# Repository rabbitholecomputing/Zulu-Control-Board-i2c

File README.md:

# Zulu control board hardware
## zulu-ctrl-board-v1.0-kicad
OLED with rotatory with a push button and two more buttons
with an I2C and an added interrupt line.

This design is derived from "ctrl_board_v1p6" in this project:
https://github.com/PiSCSI/piscsi-hw

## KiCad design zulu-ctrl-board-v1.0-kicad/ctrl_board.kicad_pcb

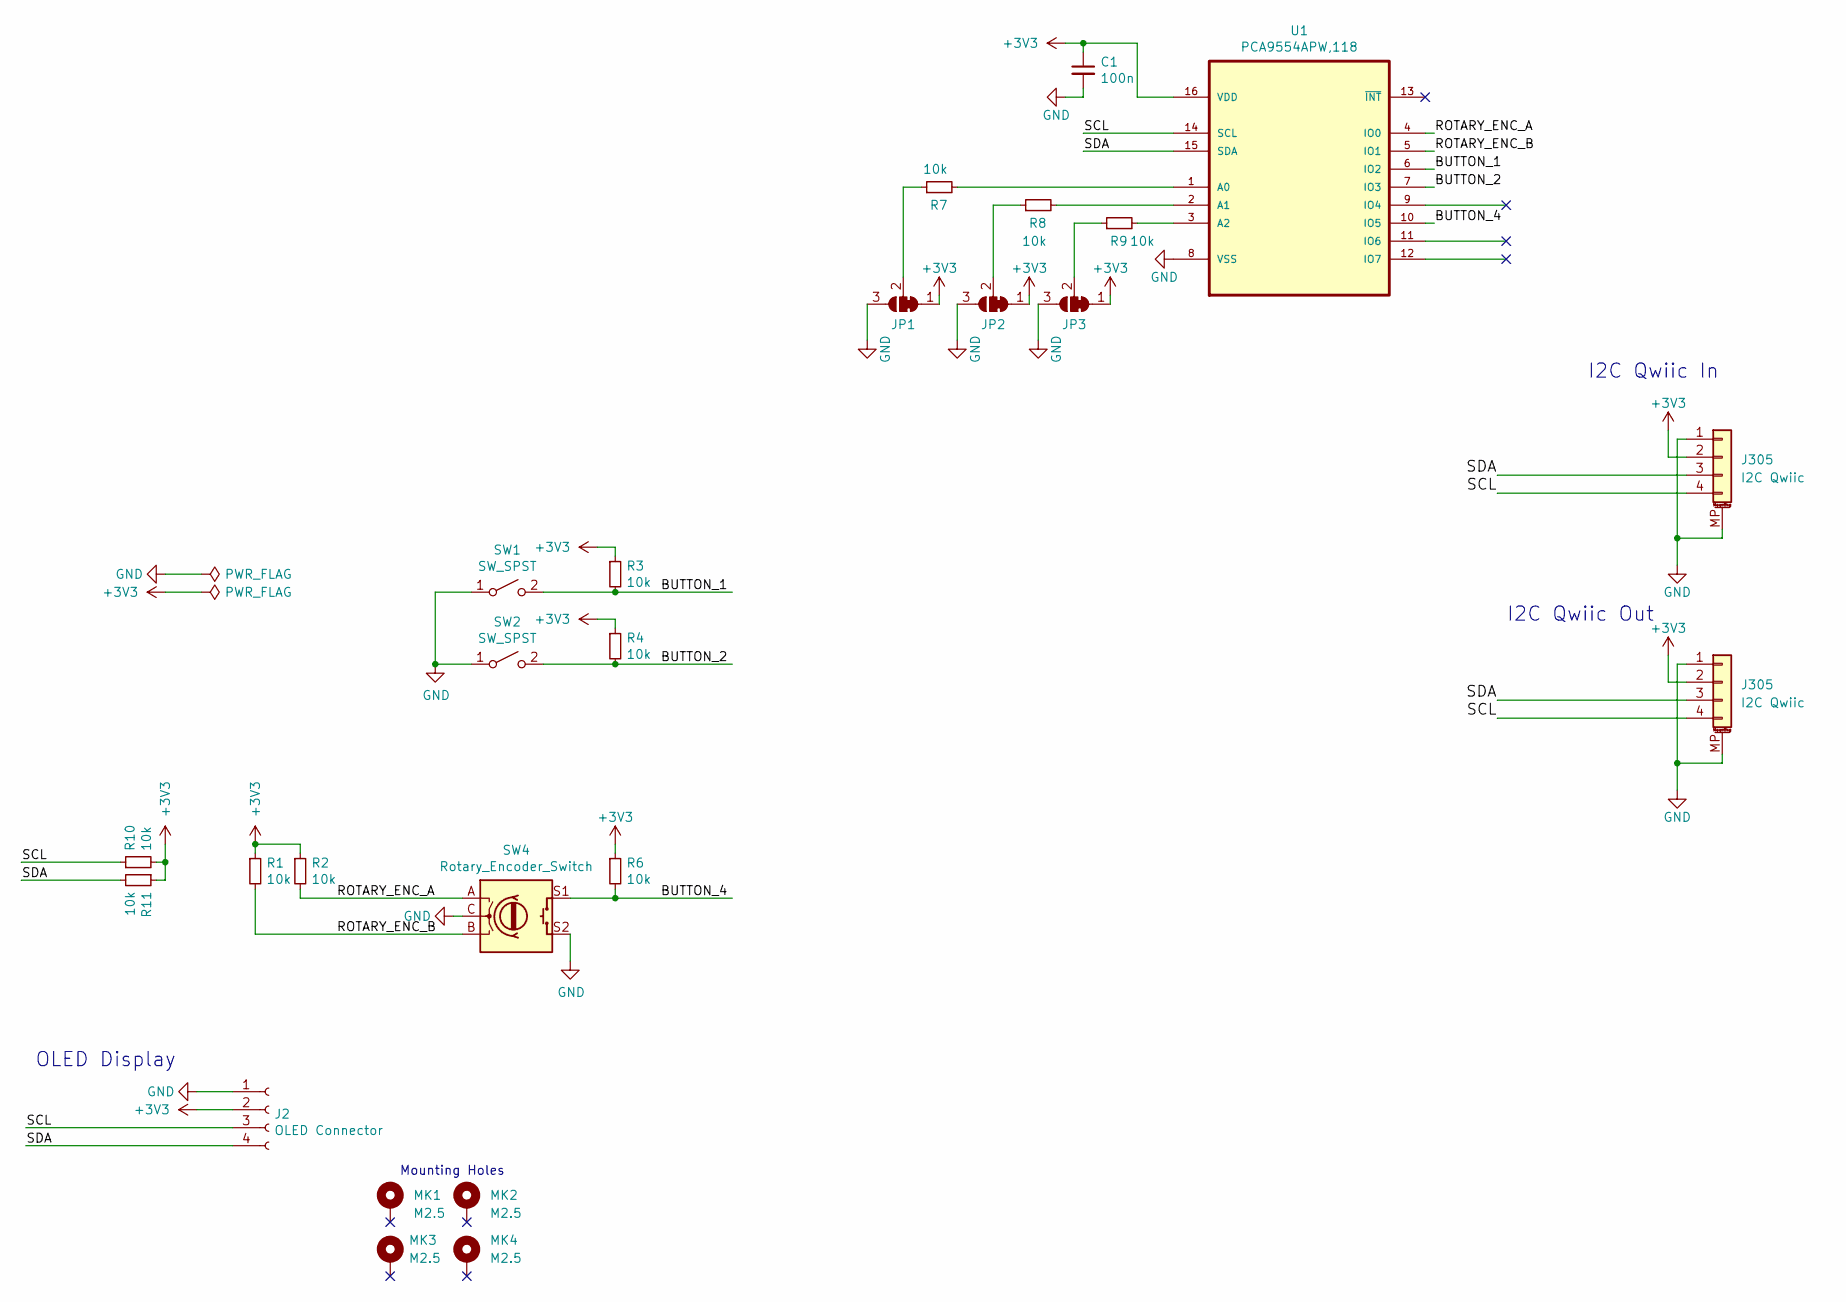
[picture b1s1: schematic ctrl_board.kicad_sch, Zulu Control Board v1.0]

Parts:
C1: 100n; C_0805_2012Metric; LCSC C49678
J2: OLED Connector; 0.9_and_1.3_in_OLED_Footprint
J305: I2C Qwiic; JST_SH_SM04B-SRSS-TB_1x04-1MP_P1.00mm_Horizontal; LCSC N/A
JP1, JP2, JP3: SolderJumper_3_Bridged12; SolderJumper-3_P1.3mm_Bridged12_RoundedPad1.0x1.5mm
MK1, MK2, MK3, MK4: M2.5; MountingHole_2.8mm_M2.5custom_DIN965_Pad
R1, R2, R3, R4, R6, R7, R8, R9, R10, R11: 10k; R_0805_2012Metric; LCSC C17414
SW1, SW2: SW_SPST; SW_PUSH_6mm_H5mm; LCSC C110153
SW4: Rotary_Encoder_Switch; RotaryEncoder_Alps_EC11E-Switch_Vertical_H20mm
U1: PCA9554APW,118; TSSOP-16_4.4x5mm_P0.65mm; MPN PCA9554APW,118; LCSC C86803

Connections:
+3V3: C1.1, J2.2, JP1.1 (A), JP2.1 (A), JP3.1 (A), R1.1, R2.1, R3.1, R4.1, R6.1, R10.2, R11.1, U1.16 (VDD); also elsewhere on the board
/BUTTON_1: R3.2, SW1.2 (B), U1.6 (IO2)
/BUTTON_2: R4.2, SW2.2 (B), U1.7 (IO3)
/BUTTON_4: R6.2, SW4.S1, U1.10 (IO5)
/ROTARY_ENC_A: R2.2, SW4.A, U1.4 (IO0)
/ROTARY_ENC_B: R1.2, SW4.B, U1.5 (IO1)
/SCL: J2.3, R10.1, U1.14 (SCL); also elsewhere on the board
/SDA: J2.4, R11.2, U1.15 (SDA); also elsewhere on the board
GND: C1.2, J2.1, JP1.3 (B), JP2.3 (B), JP3.3 (B), SW1.1 (A), SW2.1 (A), SW4.C, SW4.S2, U1.8 (VSS); also elsewhere on the board
unnamed: JP1.2 (C), R7.1
unnamed: JP2.2 (C), R8.1
unnamed: JP3.2 (C), R9.1
unnamed: R7.2, U1.1 (A0)
unnamed: R8.2, U1.2 (A1)
unnamed: R9.2, U1.3 (A2)

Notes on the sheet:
I2C Qwiic In
I2C Qwiic Out
OLED Display
Mounting Holes

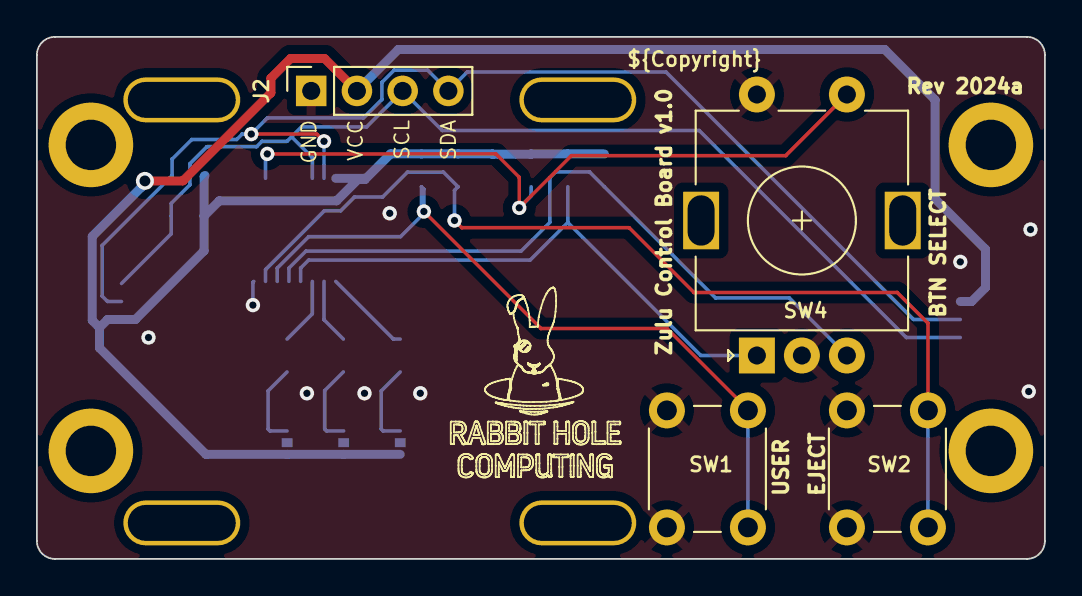
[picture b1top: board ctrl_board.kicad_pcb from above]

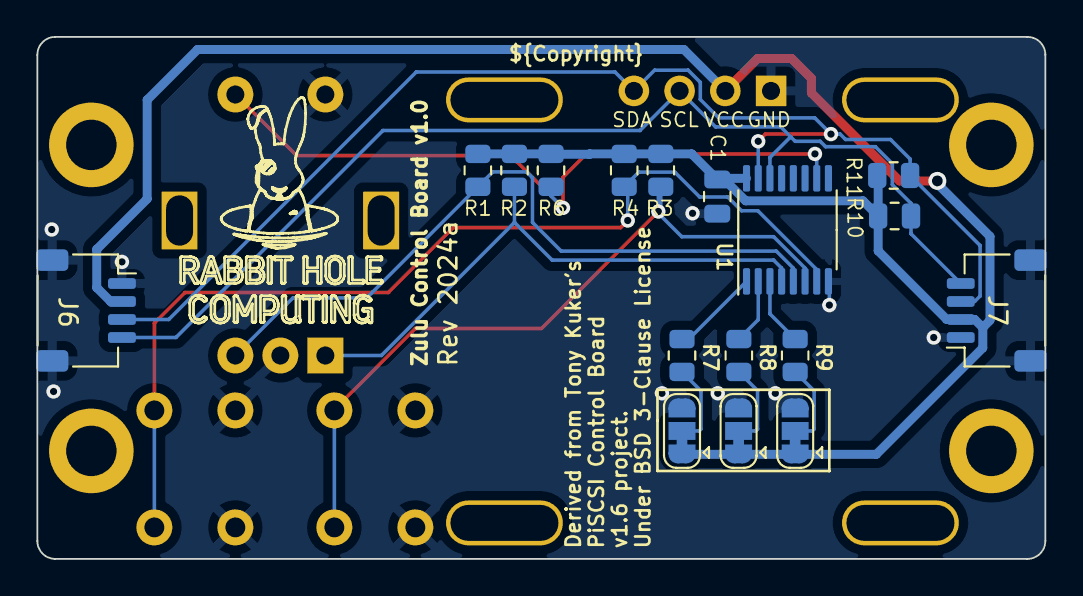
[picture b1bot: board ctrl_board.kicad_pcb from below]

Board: 2 copper layers, 56.0 x 29.0 mm, 25 parts (19 on the bottom side), 15 nets.

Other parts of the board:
J6, J7: I2C Qwiic; JST_SH_SM04B-SRSS-TB_1x04-1MP_P1.00mm_Horizontal

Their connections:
+3V3: J6.2, J7.2; also elsewhere on the board
/SCL: J6.4, J7.4; also elsewhere on the board
/SDA: J6.3, J7.3; also elsewhere on the board
GND: J6.1, J6.MP (MountPin), J7.1, J7.MP (MountPin); also elsewhere on the board

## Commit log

2024-08-05 Design of new rev
    Dropped 2.54mm pitch I2C headers, except for display
    Removed LEDs
    Added two more mounting holes. Made all 4 of them 2.8mm holes
    Decreased the size of the board
    Moved buttons, rotary, and screen closer together
2024-08-06 Add dimensions and create step file
    Added dimensions and adjusted some part locations to the nearest 0.1mm
    Generated a 3D model step file
2024-08-06 Fix filename
2024-08-06 Fix path

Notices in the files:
zulu-ctrl-board-v1.0-kicad/ctrl_board.kicad_pcb:
Under BSD 3-Clause License
parts and their libraries:
Copyright: © 2024 Rabbit Hole Computing LLC
